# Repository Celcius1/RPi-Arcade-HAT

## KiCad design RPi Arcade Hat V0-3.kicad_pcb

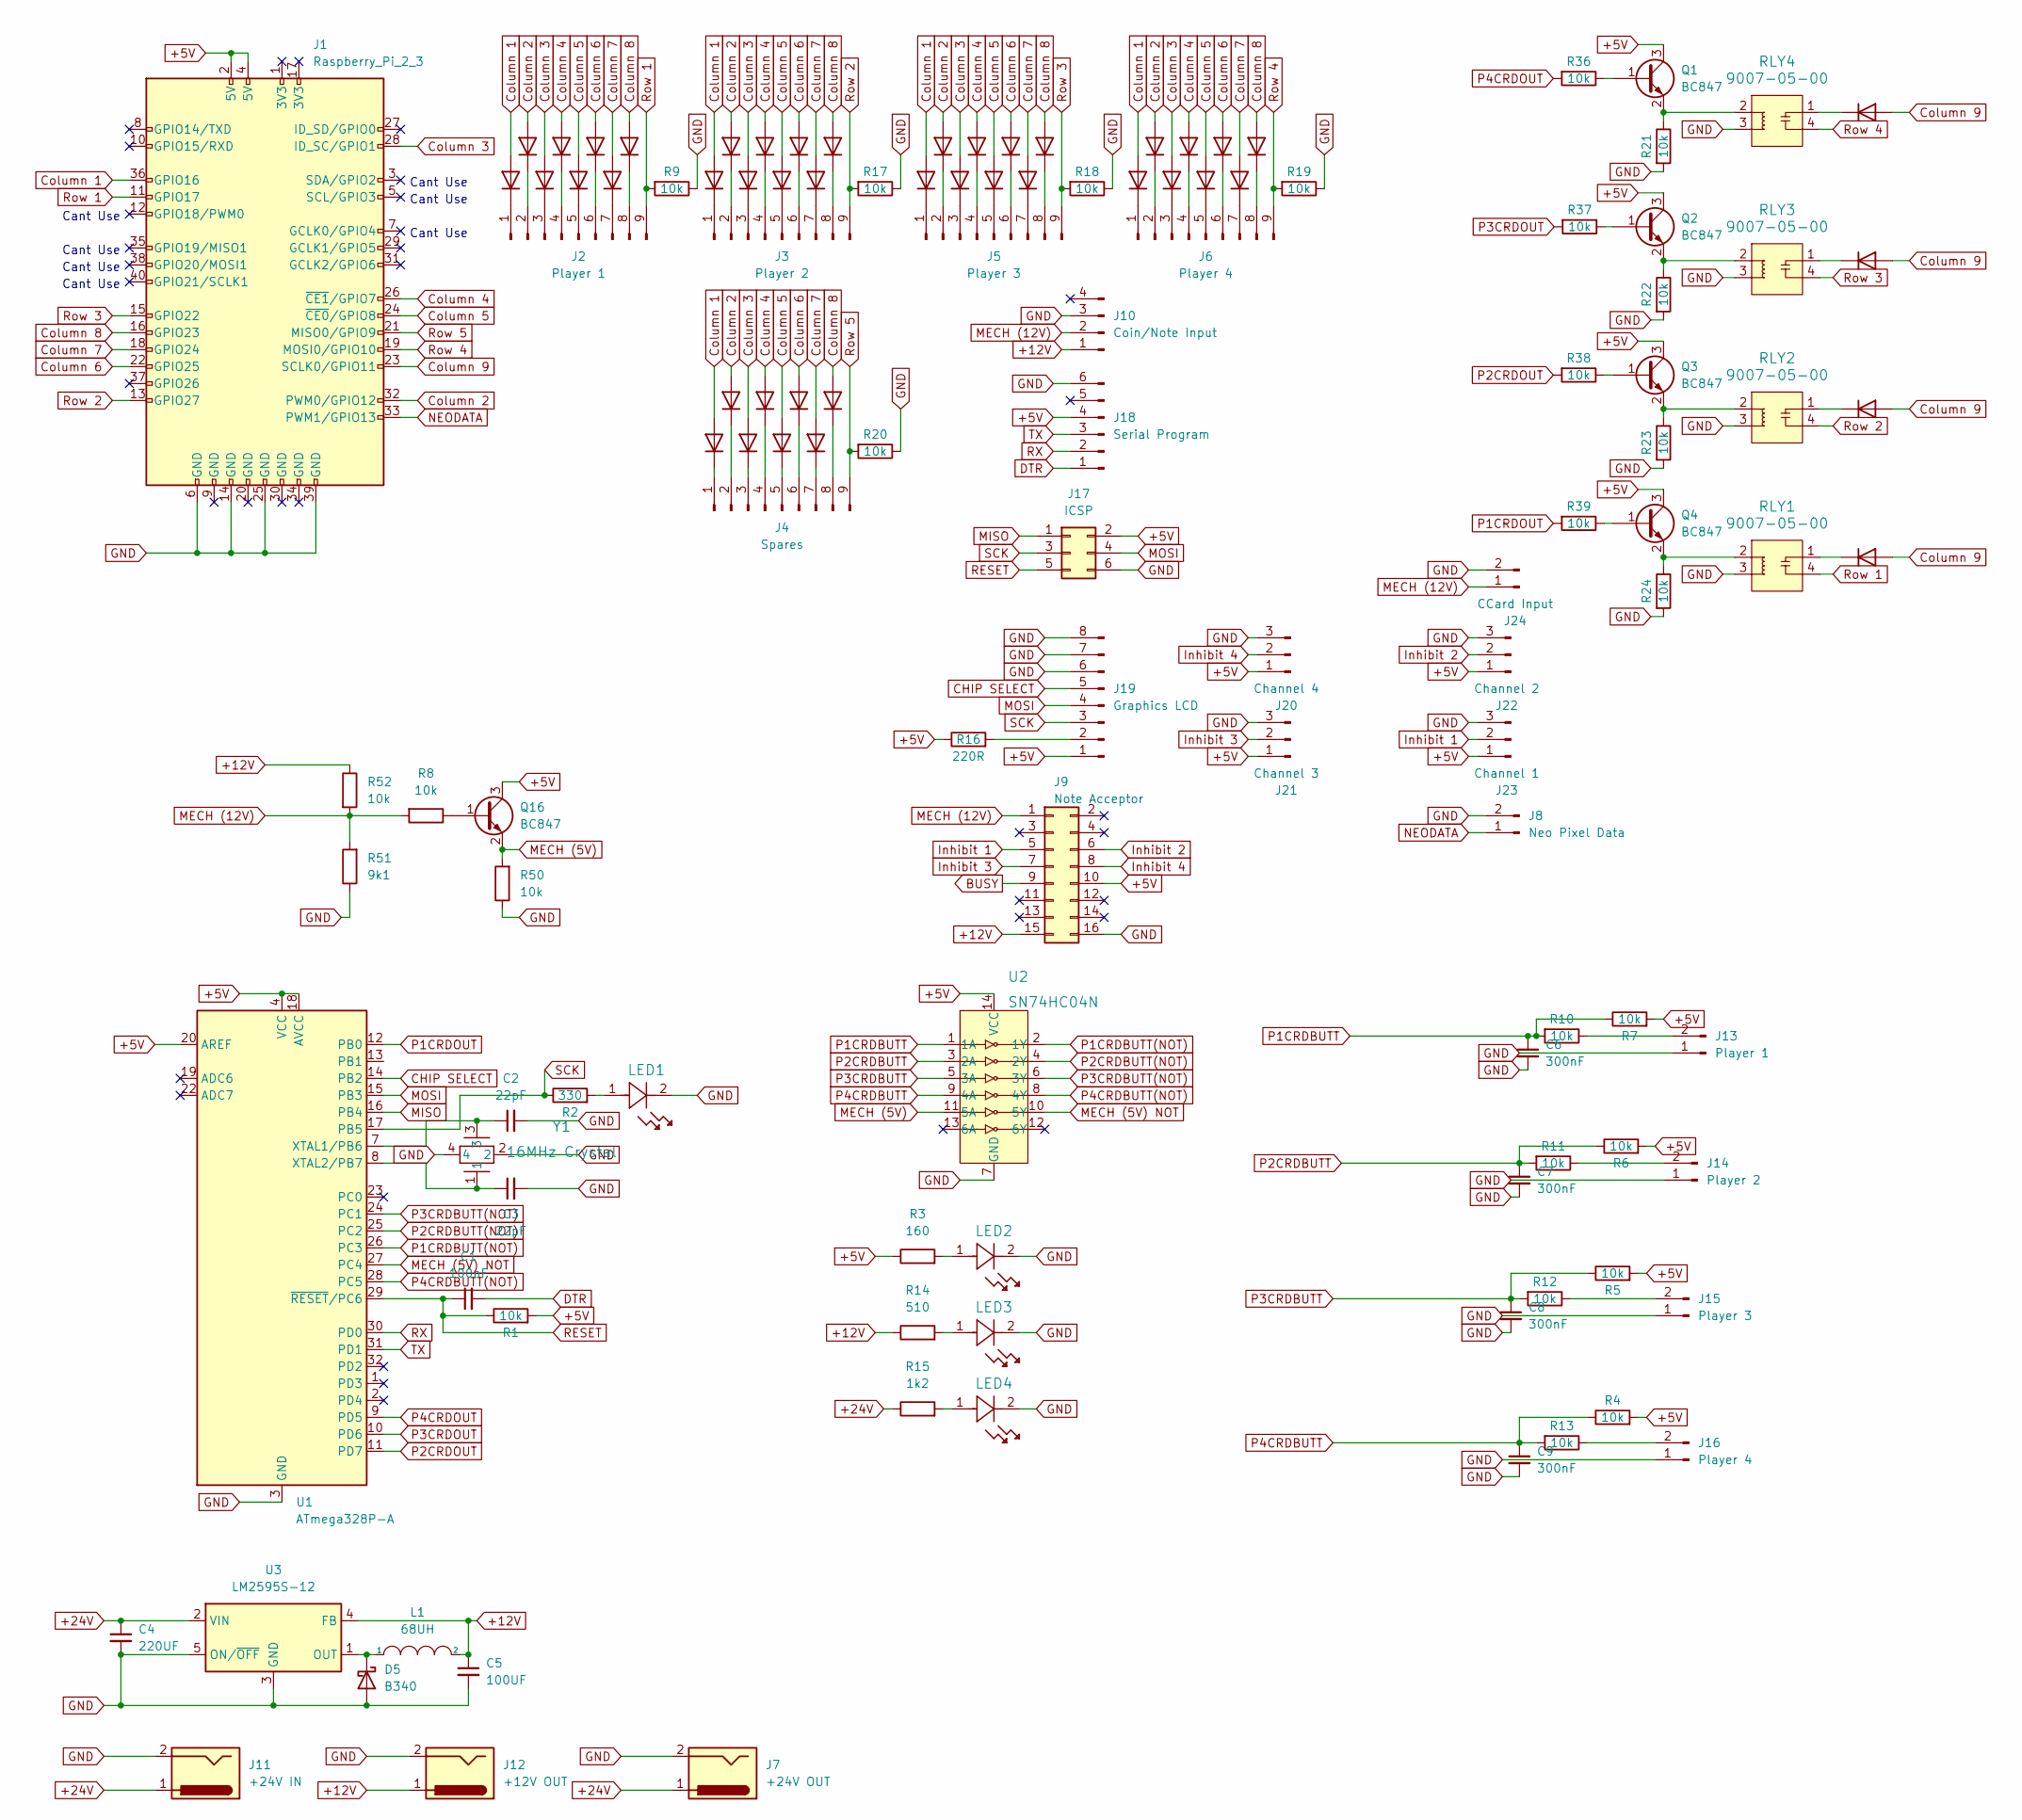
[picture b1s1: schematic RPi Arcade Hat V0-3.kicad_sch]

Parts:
C1: 100nF; C_1206_3216Metric
C2, C3: 22pF; C_1206_3216Metric
C4: 220UF; C_1210_3225Metric
C5: 100UF; C_1210_3225Metric
C6, C7, C8, C9: 300nF; C_1206_3216Metric
D1, D2, D3, D4, D6, D7, D8, D9, D10, D11, D12, D13, D14, D15, D16, D17, D18, D19, D20, D21, D22, D23, D24, D25, D26, D27, D28, D29, D30, D31, D32, D33, D34, D35, D36, D37, D38, D39, D40, D41, D42, D43, D44, D45: 1N4448W; D_SOD-123
D5: B340; D_SMC
J1: Raspberry_Pi_2_3; PinHeader_2x20_P2.54mm_Vertical
J2: Player 1; 282836-9
J3: Player 2; 282836-9
J4: Spares; 282836-9
J5: Player 3; 282836-9
J6: Player 4; 282836-9
J7: +24V OUT; BarrelJack_Horizontal
J8: Neo Pixel Data; CONN_1890963_PXC
J9: Note Acceptor; PinHeader_2x08_P2.54mm_Vertical
J10: Coin/Note Input; PinHeader_1x04_P2.54mm_Vertical
J11: +24V IN; BarrelJack_Horizontal
J12: +12V OUT; BarrelJack_Horizontal
J13: Player 1; CONN_1890963_PXC
J14: Player 2; CONN_1890963_PXC
J15: Player 3; CONN_1890963_PXC
J16: Player 4; CONN_1890963_PXC
J17: ICSP; PinHeader_2x03_P2.54mm_Vertical
J18: Serial Program; PinHeader_1x06_P2.54mm_Vertical
J19: Graphics LCD; PinHeader_1x08_P2.54mm_Vertical
J20: Channel 4; PinHeader_1x03_P2.54mm_Vertical
J21: Channel 3; PinHeader_1x03_P2.54mm_Vertical
J22: Channel 2; PinHeader_1x03_P2.54mm_Vertical
J23: Channel 1; PinHeader_1x03_P2.54mm_Vertical
J24: CCard Input; PinHeader_1x02_P2.54mm_Vertical
L1: 68UH; L_Bourns-SRN6028
LED1, LED2, LED3, LED4: 598-8270-107F; LED_8270-107F_DIA
Q1, Q2, Q3, Q4, Q16: BC847; SOT-23
R1, R4, R5, R6, R7, R8, R9, R10, R11, R12, R13, R17, R18, R19, R20, R21, R22, R23, R24, R36, R37, R38, R39, R50, R52: 10k; R_1206_3216Metric
R2: 330; R_1206_3216Metric
R3: 160; R_1206_3216Metric
R14: 510; R_1206_3216Metric
R15: 1k2; R_1206_3216Metric
R16: 220R; R_1206_3216Metric
R51: 9k1; R_1206_3216Metric
RLY1, RLY2, RLY3, RLY4: 9007-05-00; Relay_Reed_9007-05-00; MPN 9007-05-00; Digi-Key_PN 306-1062-ND
U1: ATmega328P-A; TQFP-32_7x7mm_P0.8mm
U2: SN74HC04N; SOIC-14_W3.9mm; MPN SN74HC04N; Digi-Key_PN 296-1566-5-ND
U3: LM2595S-12; TO-263-5_TabPin3
Y1: 16MHz Crystal; CRYSTAL_ABM3B_ABR

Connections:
+5V: J1.2 (5V), J1.4 (5V), J9.10, J17.2, J18.4, J19.1, J20.1, J21.1, J22.1, J23.1, Q1.3 (C), Q2.3 (C), Q3.3 (C), Q4.3 (C), Q16.3 (C), R1.2, R3.1, R4.2, R5.2, R6.2, R7.2, R16.1, U1.4 (VCC), U1.6 (VCC), U1.18 (AVCC), U1.20 (AREF), U2.14 (VCC)
+12V: C5.1, J9.15, J10.1, J12.1, L1.2, R14.1, R52.1, U3.4 (FB)
+24V: C4.1, J7.1, J11.1, R15.1, U3.2 (VIN)
BUSY: J9.9
CHIP SELECT: J19.5, U1.14 (PB2)
Column 1: D1.2 (A), D10.2 (A), D18.2 (A), D26.2 (A), D34.2 (A), J1.36 (GPIO16)
Column 2: D2.2 (A), D11.2 (A), D19.2 (A), D27.2 (A), D35.2 (A), J1.32 (PWM0/GPIO12)
Column 3: D3.2 (A), D12.2 (A), D20.2 (A), D28.2 (A), D36.2 (A), J1.28 (ID_SC/GPIO1)
Column 4: D4.2 (A), D13.2 (A), D21.2 (A), D29.2 (A), D37.2 (A), J1.26 (~CE1/GPIO7)
Column 5: D6.2 (A), D14.2 (A), D22.2 (A), D30.2 (A), D38.2 (A), J1.24 (~CE0/GPIO8)
Column 6: D7.2 (A), D15.2 (A), D23.2 (A), D31.2 (A), D39.2 (A), J1.22 (GPIO25)
Column 7: D8.2 (A), D16.2 (A), D24.2 (A), D32.2 (A), D40.2 (A), J1.18 (GPIO24)
Column 8: D9.2 (A), D17.2 (A), D25.2 (A), D33.2 (A), D41.2 (A), J1.16 (GPIO23)
Column 9: D42.2 (A), D43.2 (A), D44.2 (A), D45.2 (A), J1.23 (SCLK0/GPIO11)
DTR: C1.2, J18.1
GND: C2.2, C3.2, C4.2, C5.2, C6.2, C7.2, C8.2, C9.2, D5.2 (A), J1.6 (GND), J1.14 (GND), J1.25 (GND), J1.39 (GND), J7.2, J8.2, J9.16, J10.3, J11.2, J12.2, J13.1, J14.1, J15.1, J16.1, J17.6, J18.6, J19.6, J19.7, J19.8, J20.3, J21.3, J22.3, J23.3, J24.2, LED1.2, LED2.2, LED3.2, LED4.2, R9.1, R17.1, R18.1, R19.1, R20.1, R21.2, R22.2, R23.2, R24.2, R50.1, R51.1, RLY1.3, RLY2.3, RLY3.3, RLY4.3, U1.3 (GND), U1.5 (GND), U1.21 (GND), U2.7 (GND), U3.3 (GND), U3.5 (ON/~OFF), Y1.2, Y1.4
Inhibit 1: J9.5, J23.2
Inhibit 2: J9.6, J22.2
Inhibit 3: J9.7, J21.2
Inhibit 4: J9.8, J20.2
MECH (5V): Q16.2 (E), R50.2, U2.11 (5A)
MECH (5V) NOT: U1.27 (PC4), U2.10 (5Y)
MECH (12V): J9.1, J10.2, J24.1, R8.2, R51.2, R52.2
MISO: J17.1, U1.16 (PB4)
MOSI: J17.4, J19.4, U1.15 (PB3)
NEODATA: J1.33 (PWM1/GPIO13), J8.1
unnamed: D1.1 (K), J2.1
unnamed: D2.1 (K), J2.2
unnamed: D3.1 (K), J2.3
unnamed: D4.1 (K), J2.4
unnamed: D5.1 (K), L1.1, U3.1 (OUT)
unnamed: D6.1 (K), J2.5
unnamed: D7.1 (K), J2.6
unnamed: D8.1 (K), J2.7
unnamed: D9.1 (K), J2.8
unnamed: D10.1 (K), J3.1
unnamed: D11.1 (K), J3.2
unnamed: D12.1 (K), J3.3
unnamed: D13.1 (K), J3.4
unnamed: D14.1 (K), J3.5
unnamed: D15.1 (K), J3.6
unnamed: D16.1 (K), J3.7
unnamed: D17.1 (K), J3.8
unnamed: D18.1 (K), J5.1
unnamed: D19.1 (K), J5.2
unnamed: D20.1 (K), J5.3
unnamed: D21.1 (K), J5.4
unnamed: D22.1 (K), J5.5
unnamed: D23.1 (K), J5.6
unnamed: D24.1 (K), J5.7
unnamed: D25.1 (K), J5.8
unnamed: D26.1 (K), J6.1
unnamed: D27.1 (K), J6.2
unnamed: D28.1 (K), J6.3
unnamed: D29.1 (K), J6.4
unnamed: D30.1 (K), J6.5
unnamed: D31.1 (K), J6.6
unnamed: D32.1 (K), J6.7
unnamed: D33.1 (K), J6.8
unnamed: D34.1 (K), J4.1
unnamed: D35.1 (K), J4.2
unnamed: D36.1 (K), J4.3
unnamed: D37.1 (K), J4.4
unnamed: D38.1 (K), J4.5
unnamed: D39.1 (K), J4.6
unnamed: D40.1 (K), J4.7
unnamed: D41.1 (K), J4.8
unnamed: D42.1 (K), RLY4.1
unnamed: D43.1 (K), RLY3.1
unnamed: D44.1 (K), RLY2.1
unnamed: D45.1 (K), RLY1.1
unnamed: J13.2, R10.1
unnamed: J14.2, R11.1
unnamed: J15.2, R12.1
unnamed: J16.2, R13.1
unnamed: J19.2, R16.2
unnamed: LED1.1, R2.2
unnamed: LED2.1, R3.2
unnamed: LED3.1, R14.2
unnamed: LED4.1, R15.2
unnamed: Q1.1 (B), R36.1
unnamed: Q1.2 (E), R21.1, RLY4.2
unnamed: Q2.1 (B), R37.1
unnamed: Q2.2 (E), R22.1, RLY3.2
unnamed: Q3.1 (B), R38.1
unnamed: Q3.2 (E), R23.1, RLY2.2
unnamed: Q4.1 (B), R39.1
unnamed: Q4.2 (E), R24.1, RLY1.2
unnamed: Q16.1 (B), R8.1
unnamed: C2.1, U1.7 (XTAL1/PB6), Y1.3
unnamed: C3.1, U1.8 (XTAL2/PB7), Y1.1
P1CRDBUTT: C6.1, R7.1, R10.2, U2.1 (1A)
P1CRDBUTT(NOT): U1.26 (PC3), U2.2 (1Y)
P1CRDOUT: R39.2, U1.12 (PB0)
P2CRDBUTT: C7.1, R6.1, R11.2, U2.3 (2A)
P2CRDBUTT(NOT): U1.25 (PC2), U2.4 (2Y)
P2CRDOUT: R38.2, U1.11 (PD7)
P3CRDBUTT: C8.1, R5.1, R12.2, U2.5 (3A)
P3CRDBUTT(NOT): U1.24 (PC1), U2.6 (3Y)
P3CRDOUT: R37.2, U1.10 (PD6)
P4CRDBUTT: C9.1, R4.1, R13.2, U2.9 (4A)
P4CRDBUTT(NOT): U1.28 (PC5), U2.8 (4Y)
P4CRDOUT: R36.2, U1.9 (PD5)
RESET: C1.1, J17.5, R1.1, U1.29 (~RESET/PC6)
RX: J18.2, U1.30 (PD0)
Row 1: J1.11 (GPIO17), J2.9, R9.2, RLY1.4
Row 2: J1.13 (GPIO27), J3.9, R17.2, RLY2.4
Row 3: J1.15 (GPIO22), J5.9, R18.2, RLY3.4
Row 4: J1.19 (MOSI0/GPIO10), J6.9, R19.2, RLY4.4
Row 5: J1.21 (MISO0/GPIO9), J4.9, R20.2
SCK: J17.3, J19.3, R2.1, U1.17 (PB5)
TX: J18.3, U1.31 (PD1)

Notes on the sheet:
Cant Use

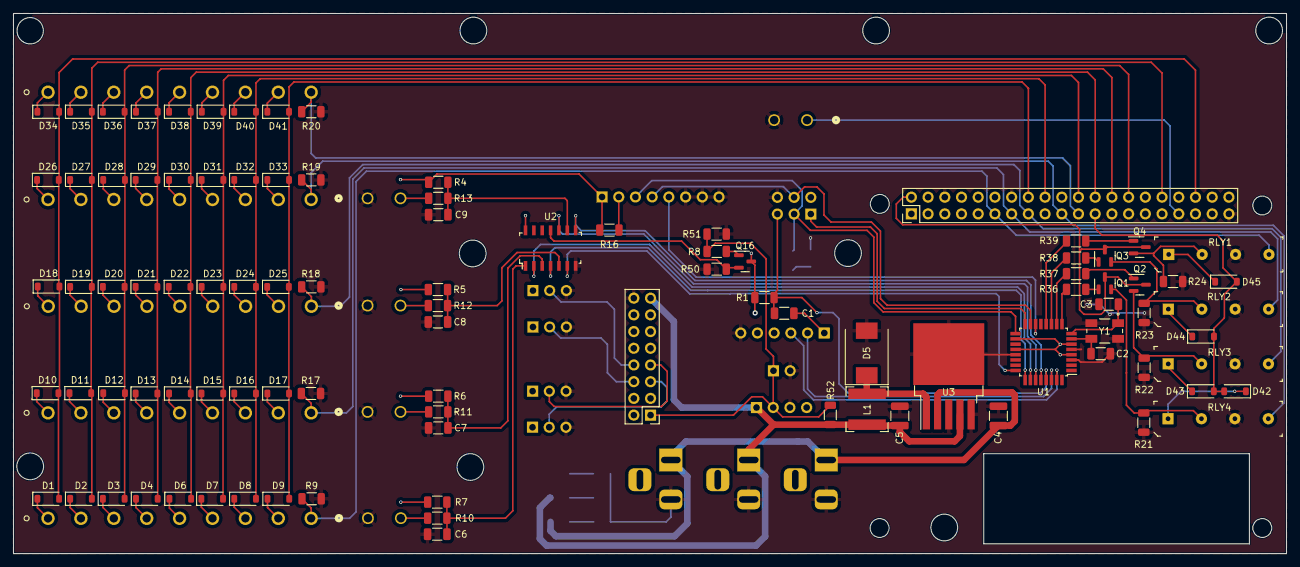
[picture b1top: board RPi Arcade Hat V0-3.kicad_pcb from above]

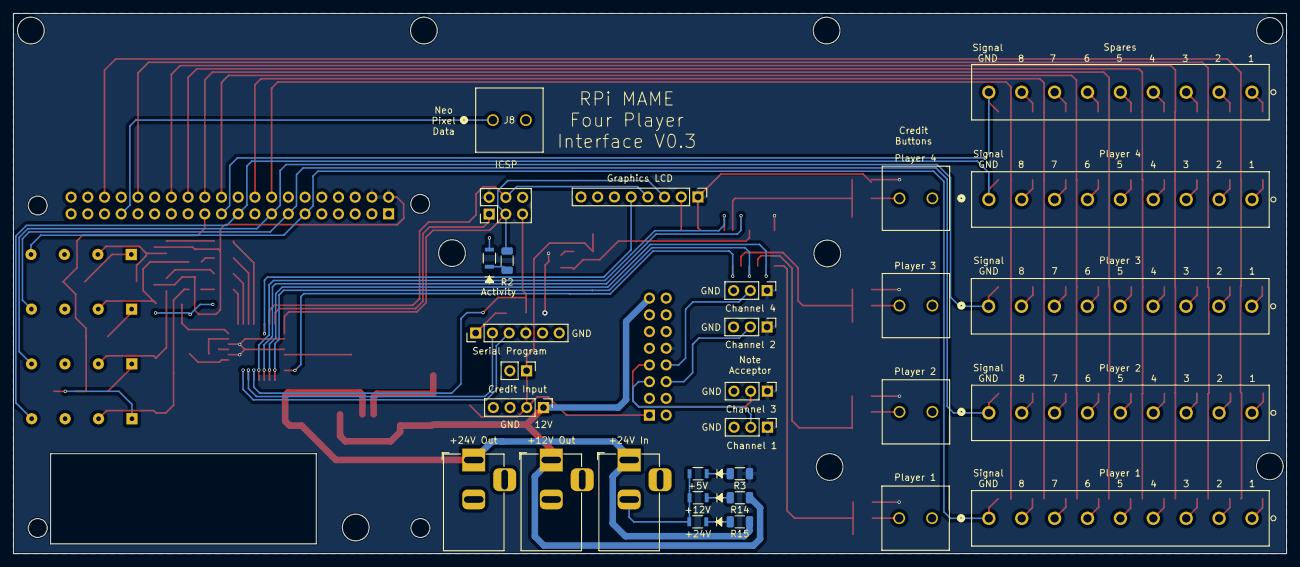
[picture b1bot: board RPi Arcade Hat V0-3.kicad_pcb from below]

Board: 2 copper layers, 193.5 x 82.1 mm, 127 parts (30 on the bottom side), 111 nets.

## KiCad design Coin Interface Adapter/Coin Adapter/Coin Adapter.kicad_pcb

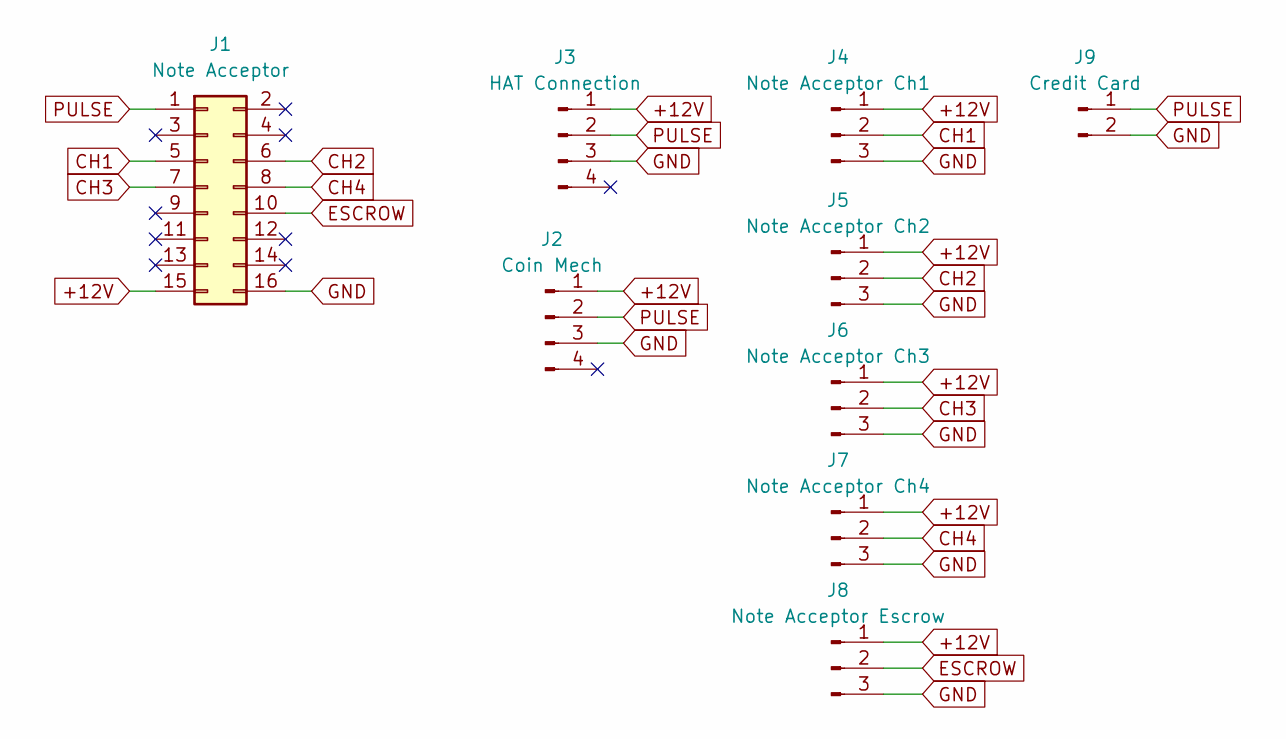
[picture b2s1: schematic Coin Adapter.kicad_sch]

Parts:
J1: Note Acceptor; PinHeader_2x08_P2.54mm_Vertical
J2: Coin Mech; PinHeader_1x04_P2.54mm_Vertical
J3: HAT Connection; PinHeader_1x04_P2.54mm_Vertical
J4: Note Acceptor Ch1; PinHeader_1x03_P2.54mm_Vertical
J5: Note Acceptor Ch2; PinHeader_1x03_P2.54mm_Vertical
J6: Note Acceptor Ch3; PinHeader_1x03_P2.54mm_Vertical
J7: Note Acceptor Ch4; PinHeader_1x03_P2.54mm_Vertical
J8: Note Acceptor Escrow; PinHeader_1x03_P2.54mm_Vertical
J9: Credit Card; PinHeader_1x02_P2.54mm_Vertical

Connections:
+12V: J1.15, J2.1, J3.1, J4.1, J5.1, J6.1, J7.1, J8.1
CH1: J1.5, J4.2
CH2: J1.6, J5.2
CH3: J1.7, J6.2
CH4: J1.8, J7.2
ESCROW: J1.10, J8.2
GND: J1.16, J2.3, J3.3, J4.3, J5.3, J6.3, J7.3, J8.3, J9.2
PULSE: J1.1, J2.2, J3.2, J9.1

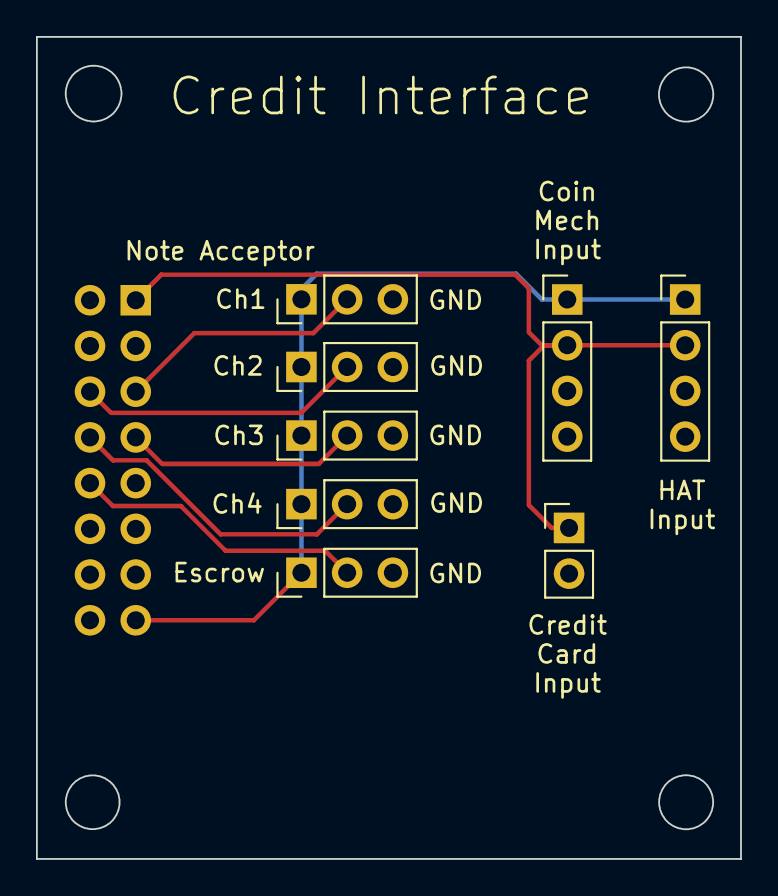
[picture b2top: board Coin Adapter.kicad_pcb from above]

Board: 2 copper layers, 39.1 x 45.7 mm, 9 parts (1 on the bottom side), 8 nets.

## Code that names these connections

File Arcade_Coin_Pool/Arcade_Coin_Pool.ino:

#include <Arduino.h>
#include <U8g2lib.h>
#include <SPI.h>
#include "stdlib.h"
#include <Wire.h>
#include <avr/interrupt.h>

// Coin Mech on Pin 27 PC4 DIO A4  Output goes High to Add to Credit Pool
// P1 Credit Allocation on Pin 10 PD6 DIO 6
// P1 Credit Input to RPi on Pin 25 PC2 DIO A2 Output goes High to Apply Credit
// P2 Credit Allocation on Pin 11 PD7 DIO 7
// P2 Credit Input to RPi on Pin 26 PC3 DIO A3 Output goes High to Apply Credit
// P3 Credit Allocation on Pin 13 PB1 DIO 9
// P3 Credit Input to RPi on Pin 12 PB0 DIO 8 Output goes High to Apply Credit
// P4 Credit Allocation on Pin 28 PC5 DIO A5
// P4 Credit Input to RPi on Pin 9 PD5 DIO 5 Output goes High to Apply Credit

// assigned Pins ATMega 328P TQFP
int coinMech = 18;
int PlayC1A = 17;
int PlayI1 = 8;
int PlayC2A = 16;
int PlayI2 = 7;
int PlayC3A = 15;
int PlayI3 = 6;
int PlayC4A = 19;
int PlayI4 = 5;

//const
int coins = 0;

//variables
int timer1_match;


//boolean
volatile bool creditState = false;
volatile bool twoPlayer = false;
volatile bool playerState1 = false;
volatile bool playerState2 = false;
volatile bool playerState3 = false;
volatile bool playerState4 = false;

volatile char tempStore1[10];

U8G2_ST7920_128X64_1_HW_SPI u8g2(U8G2_R0, /* CS=*/ 10, /* reset=*/ 22);


void setup(void) {
  cli();
  TCCR1A = 0;
  TCCR1B = 0;
  timer1_match = 10;
  TCNT1 = timer1_match;
  TCCR1B |= (1 << CS11);
  //TCCR1B |= (1 << CS10);
  TIMSK1 |= (1 << OCIE1A);
  sei();
//Serial.begin(9600);

//Pin Allocations
  pinMode(coinMech, INPUT_PULLUP);
  pinMode(PlayC1A, INPUT_PULLUP);
  pinMode(PlayC2A, INPUT_PULLUP);
  pinMode(PlayC3A, INPUT_PULLUP);
  pinMode(PlayC4A, INPUT_PULLUP);
  pinMode(PlayI1, OUTPUT);
  pinMode(PlayI2, OUTPUT);
  pinMode(PlayI3, OUTPUT);
  pinMode(PlayI4, OUTPUT);
  if(digitalRead(PlayC4A) == HIGH)
  {
    twoPlayer = !twoPlayer;
  }
  u8g2.begin();
}

void loop(void) {
  u8g2.firstPage();
  do {
    dtostrf(coins, 2, 0, tempStore1);
    u8g2.setFont(u8g2_font_fub14_tf);
    u8g2.drawStr(20,25,"Coin Pool");
    if(twoPlayer != HIGH)
    {
      u8g2.drawStr(2,50,"Credits: $");
      u8g2.drawStr(98,50,tempStore1);
    }
    else
    {
      u8g2.drawStr(25,50,"Disabled");
    }
    
  } while ( u8g2.nextPage() );
}
ISR(TIMER1_COMPA_vect)
{
  TCNT1 = timer1_match;
  if(digitalRead(coinMech) == HIGH && creditState == LOW && twoPlayer == LOW)
  {
    creditState = !creditState;
    coins++;
  }
  if(digitalRead(coinMech) == LOW && creditState == HIGH && twoPlayer == LOW)
  {
    creditState = !creditState;
  }
  if(digitalRead(coinMech) == HIGH && creditState == LOW && twoPlayer == HIGH)
  {
    creditState = !creditState;
    digitalWrite(PlayI1, HIGH);
  }
  if(digitalRead(coinMech) == LOW && creditState == HIGH && twoPlayer == HIGH)
  {
    creditState = !creditState;
    digitalWrite(PlayI1, LOW);
  }
  if(digitalRead(PlayC4A) == HIGH && playerState4 == LOW)
  {
    playerState4 = !playerState4;
    if (coins!=0)
    {
      coins--;
      digitalWrite(PlayI4, HIGH);
    }
  }
  if(digitalRead(PlayC4A) == LOW && playerState4 == HIGH)
  {
    digitalWrite(PlayI4, LOW);
    playerState4 = !playerState4;
  }
  
  if(digitalRead(PlayC3A) == HIGH && playerState3 == LOW)
  {
    playerState3 = !playerState3;
    if (coins!=0)
    {
      coins--;
      digitalWrite(PlayI3, HIGH);
    }
  }
  if(digitalRead(PlayC3A) == LOW && playerState3 == HIGH)
  {
    digitalWrite(PlayI3, LOW);
    playerState3 = !playerState3;
  }

  if(digitalRead(PlayC2A) == HIGH && playerState2 == LOW)
  {
    playerState2 = !playerState2;
    if (coins!=0)
    {
      coins--;
      digitalWrite(PlayI2, HIGH);
    }
  }
  if(digitalRead(PlayC2A) == LOW && playerState2 == HIGH)
  {
    digitalWrite(PlayI2, LOW);
    playerState2 = !playerState2;
  }

  if(digitalRead(PlayC1A) == HIGH && playerState1 == LOW)
  {
    playerState1 = !playerState1;
    if (coins!=0)
    {
      coins--;
      digitalWrite(PlayI1, HIGH);
    }
  }
  if(digitalRead(PlayC1A) == LOW && playerState1 == HIGH)
  {
    digitalWrite(PlayI1, LOW);
    playerState1 = !playerState1;
  }
}

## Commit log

2023-06-07 Initial Upload
2023-06-17 Error fixed
    Found a wiring error in the circuit for the credit input, had it wired for NC logic (Active High), when should've been NO(Active Low)
2023-06-18 PCB Redesigned as a Four Layer Board
    I decided to redesign the PCB utilising screw terminals instead of IDC plugs, also made the PCB into a four layer board and Generated gerber's need to fix some silk screen details
2023-06-19 Minor Refinements, and Final Gerbers
    Made some final refinements, and made sure that silkscreens were also correct before getting PCB's made
2023-06-19 Adjusted PCB so it will manufacture as one
    JLCPCB had issues with the gerbers adjusted so it is seen as one design otherwise extra processing fees would apply
2023-06-20 Found Error on Debounce Circuit
    As I was going through the schematic I found I wired the button credit input incorrect, and had the logic level held high then pulling to GND, and I should've used an inverter on the output, went wit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
2023-06-20 Reverted Changes
2023-06-21 Current Changes To Repository
2023-07-12 Board Redesign
    As ATMega328 are back in stock I have returned to using a MCU and adjust the design now it is a double sided design and not an expensive multi layered design
2023-07-13 Adjust Design to PCBWay limitations
2023-07-13 Updated to KiCAD 7 format
2023-07-20 updated backups
2023-08-03 Added Arduino Code
2023-08-12 Changes made after testing
2023-08-24 Fixed Input Matrix
2023-09-16 Additional Fixes
2024-01-26 fixes and updates

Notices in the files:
parts and their libraries:
Copyright 2021 Accelerated Designs. All rights reserved.
